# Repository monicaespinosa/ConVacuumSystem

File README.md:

# ConVacuumSystem
Later I will have time to explain what this is about. Let's start with the important things.

## Current circuit
The circuit (still to try) goes as following:

The setup still has to be simulated to find out V_c and to check the accuracy of the voltages selected for the grid and the plate.

## CST Simulations of the setup
The following setup was simulated:

Initially were the following voltages set:
* V_S 6.4 V
* V_C: 6.4 V
* V_G= 400 V
* V_P= 1000 V

The result for the obtained trajectory is shown below. The obtained current was around 5 mA.

However, the shape of the electron beams seems to change its shape in a very drastic way. Making the V_C smaller (more negative) should help concentring more the electrons to the center of the beam. A second simulation was made sweeping the voltage of the Wehnelt_Cylinider between -10 V and 6 V. 

As a result, the following charges on the plate were obtained:

Particles that come out of the coil:

They are only high when the voltage at the Wehnelt Cylinider is equal or higher than that of the coil. A new simulation sweeping Vc between 6.4V and 15.4V is been made. Results:

Evidently, the current (and as a consequence the particles getting to the plate) exists only when V_C>=V_S. The trajectories of the particles change however as they seem to be pushed into the cylinder (because of the higher voltage):

A new simulation setting the voltage on the grid V_G=800 V, putting a porcelain cylinder around the components (to simulate the glass cylinider) and moving the cylinider along the z-axis was made. The obtained trajectories are:

### Setting the voltage on the plate nearly to 0
Simulation with V_G = 1000 V and V_P = 4 V, and moving the cylinder to its initial position.

Simulation with the same parameters but moving the cylinder so its positioned closer to the plate.

Final simulation moving the cylinder back again and setting its voltage to -V_S.

### Variations of the voltage on the plate

Current incoming to the plate is the import_2 current.

Incoming particles:

### Changing the cathode
For all the following simulations the following voltages are set: V_S=6.4V, V_C=-30V V_G = 1000V and V_P = 4V.

#### Vertical filled PEC cylinder
Model:

Trajectories:

Total current leaving the cathode: 1.191e-03 mA

### Vertical hollow PEC cylinder
The cathode looks like the one before but is hollow with a thickness of 0.3 mm.

Trajectories:

Total current leaving the cathode: 9.14e-02 mA

### Toroid
Model:

Trajectories:

Total current leaving the cathode: 0.98 mA

### Rectangular cathode:
Model:

Trajectories: 

Total current leaving the cathode: 0.78 mA

### Sphere
Model:

Trajectories:

Total current leaving the cathode: 1.19 mA

### cut Cone:
Model:

It didn't emit any current when being put this way. However, when rotating like this:

The following trajectories are gotten:

Total current leaving the cathode: 0.71 mA

### Electron-gun Cathode
Model: 

It's a "cone" whose two planar circular faces are connected not by a rotated linear surface but a rotated exponential surface so it's internal radious get's thicker in an exponential way along the w axis as w decreases, simulating a pointy trunked cone. It was initially made small but only few particles were accelerated. Increasing its size and getting it closer to the grid produces the following trajectories:

The total current leaving the cathode was 9.35 mA. However the trajectories are messy and very disperse. After trying to move both the cathode and the grid further from the plate, because of the Wehnelt-Cylinder, the particles collide and then get dispersed again, without reaching the plate:

### Toroid-Coil

Model:

Trajectories: (actually a pretty straight beam)

However, the current incoming to the plate was not as high as expected. In this case, a variation of the voltage on the plate was made and the following curve obtained:

A dependency of the current to the voltage on the grid was also tested. The results below show in fact that the highest this voltage is, the highest the current.

As the shape of the beam seems to be well centered, another try using two toroids was given a shot. The model of the cathode goes as following:

As expected, the trajectories:

However the current across the platte is 50 uA. 

### Clapton Coil
This is the coil used normally for vapers. One of these was modelled in CST and looks like this:

The current incoming into the plate is 21.46uA. However, as the clapton coils that are found in the market have typically a diameter of 3.0mm, which for this project is too small. In order to increase the size of the cathode, a few of them can be placed together. For this purpose, four clapton coils forming a loop was simulated:

Trajectories: Not so straight directed to the center of the beam.

Current incoming to the plate: 0.18 mA

## Current measurement

### Methode
As mentioned before, this is the electrical structure of the setup:

The current measurement in between the plate and the voltage source V_p is more detailed here:

The current flowing through R_mess is theorically expected to be around 5mA according to the simulations. Supposing that the current is 10mA, the following circuit was simulated to choose the value of R_mess:

The voltage across Rm increases as Rm does. A value of Rm=140 ohm is temporarily chosen.

The following component is a amplifier that measures the voltage across the resistor R_mess and whose output is a digital signal whose amount of 1's is proportional to the current flowing through R_mess. The used amplifier is the Si8946A, that measures voltages between -62.5 mV and +62.5 mV, and whose output has a frequency of 10MHz. As this frequency is too high for a microcontroller like Arduino to read, a phase of signal conditioning is required. The simple RC filter produces an analog signal which corresponds to an average value of the quantity of 1's contained in the digital output of the amplifier. As this output is either a 0 or a 1, the analog response of the filter varies between 0V to 1V. However, as we intend to read this signal with Arduino, in order to take of advantage of all its measuring range the to-be-measured signal should be in the full range of 0V to 5V. This is the reason why an additional operational amplifier with a gain of 5 is used. The amplifier corresponds to the TLV9001 by Texas Instruments.

### PCB

The whole circuitry mentioned above, intended to be used for measuring the current caused by the electrons colliding into the plate and further flowing through R_mess, will be designed to be as close as posible to the plate. As not only the amount of current is important, but also the distribution of the electrons along the plate, this last is eventually going to be divided into many smaller plates whose incoming current will be measured separatedly. The first PCB designed to try the measuring circuitry has three plates. The PCB has two layers, one of them containing the plates

and the other one the Si8946A amplifiers and the connector in charge of providing feeding voltage and of letting the signals out. 

To know if the digital signal at 10 MHz is able to be carried by a normal jumper cable without using a SMA connector, some calculations need to be made:

Let's assume a square wave and use Bogatins rule of thumb [here](https://www.edn.com/rule-of-thumb-1-bandwidth-of-a-signal-from-its-rise-time/). According to the datasheet, the rise time is 20ns. The bandwidth of such a signal is 50 MHz, whose wavelength in free space is 6m, let's say 3m in the PCB. At 1/10th wavelength that's 30cm, which sets the upper limit to the jumper wire's length. 

Another option is to attach a second PCB using a PCB to PCB connector. 

>>>>>>> main

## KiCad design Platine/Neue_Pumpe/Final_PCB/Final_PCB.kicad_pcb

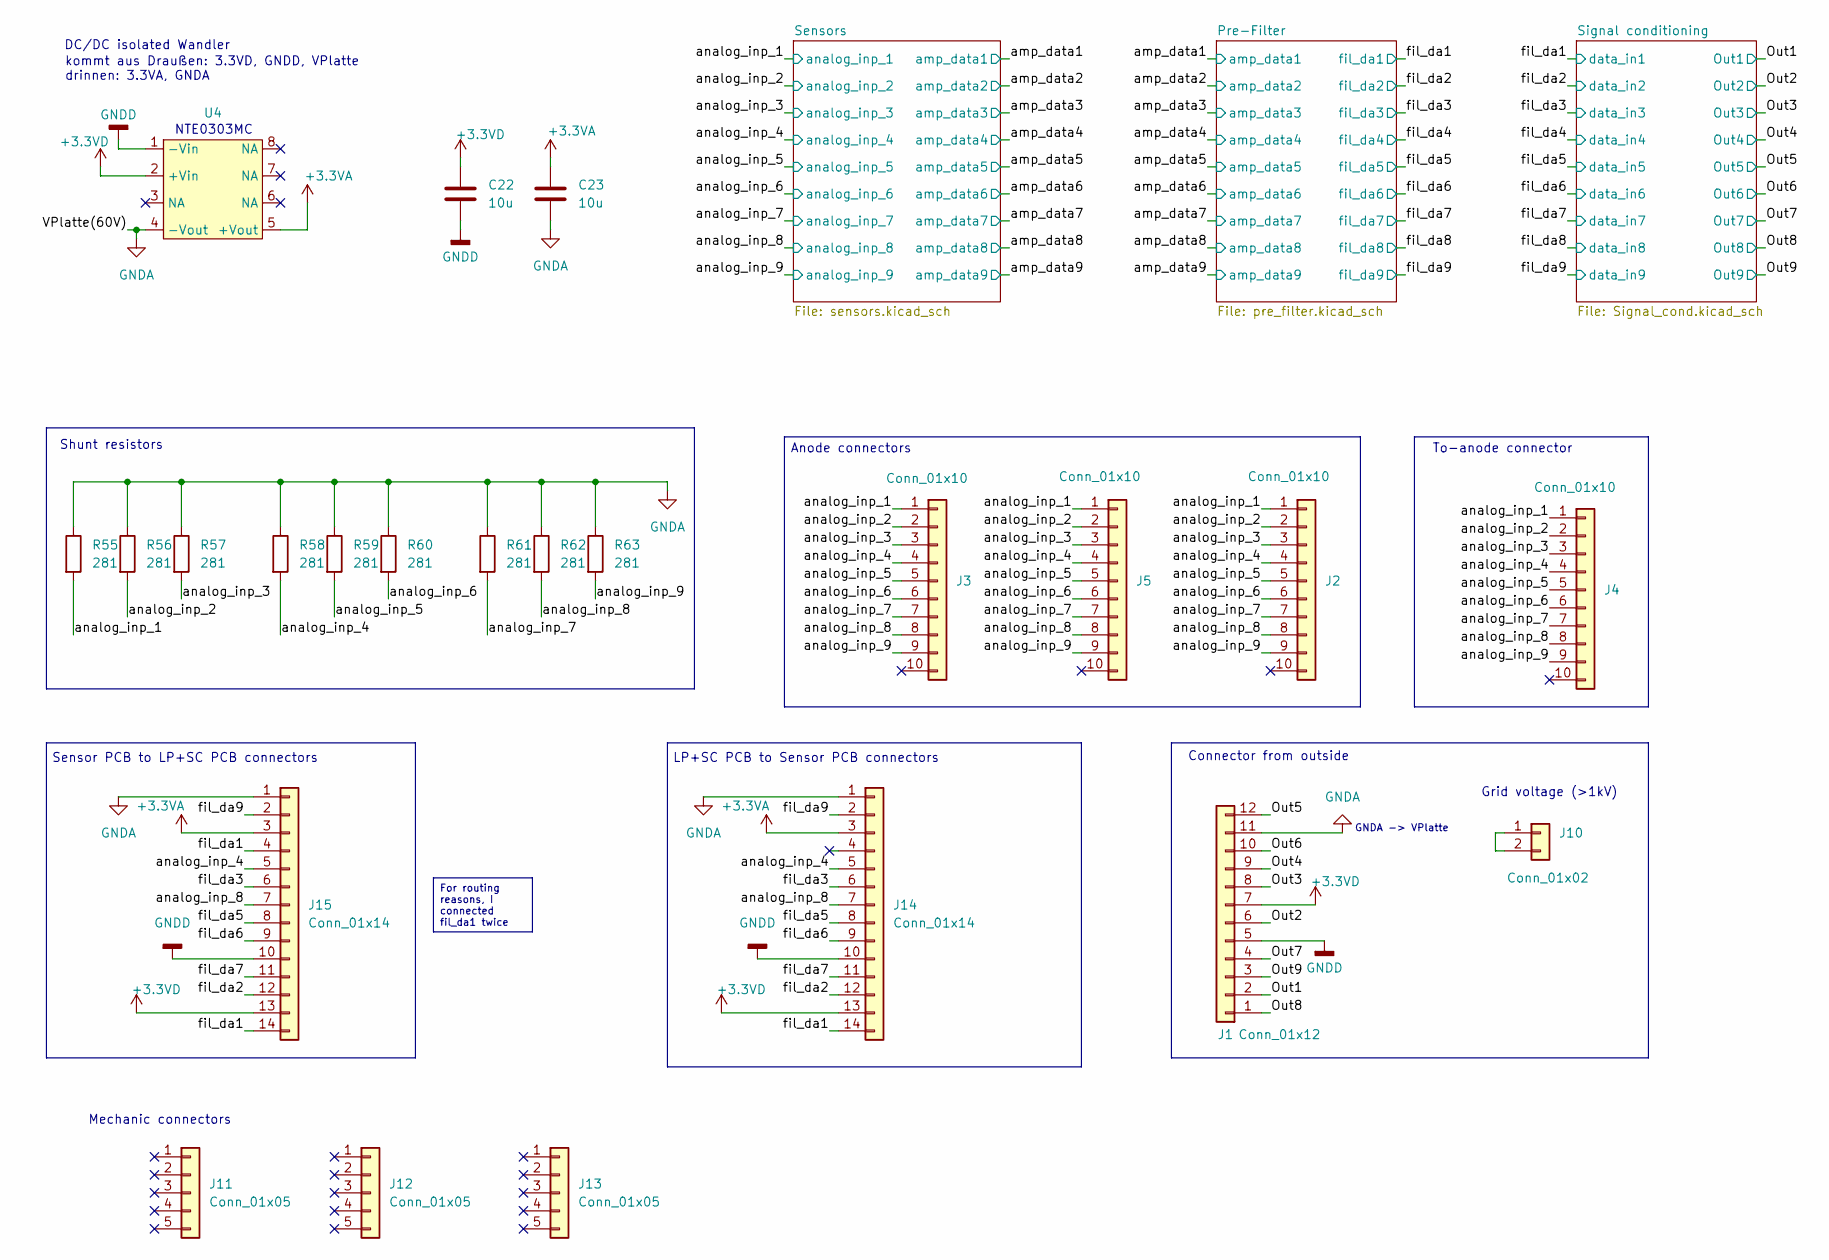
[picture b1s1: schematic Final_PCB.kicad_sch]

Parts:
C22, C23: 10u; C_0603_1608Metric_Pad1.08x0.95mm_HandSolder
J1: Conn_01x12; SHF-106-01-L-D-SM
J2, J3, J5: Conn_01x10; FLE-105-01-X-DV-Y-TR
J4: Conn_01x10; FTSH-105-01-L-DV-K
J10: Conn_01x02; OST_OSTTE020104
J11, J12, J13: Conn_01x05; PinHeader_1x05_P1.27mm_Vertical
J14: Conn_01x14; SAMTEC_FTS-107-01-L-D
J15: Conn_01x14; SAMTEC_FTSH-107-01-L-DV-K
R55, R56, R57, R58, R59, R60, R61, R62, R63: 281; R_0603_1608Metric_Pad0.98x0.95mm_HandSolder
U4: SMDIP-8_W9.53mm

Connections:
+3.3VA: C23.2, J14.3, J15.3, U4.5 (+Vout); also elsewhere on the board
+3.3VD: C22.2, J1.7, J14.13, J15.13, U4.2 (+Vin); also elsewhere on the board
/Out1: J1.2; also elsewhere on the board
/Out2: J1.6; also elsewhere on the board
/Out3: J1.8; also elsewhere on the board
/Out4: J1.9; also elsewhere on the board
/Out5: J1.12; also elsewhere on the board
/Out6: J1.10; also elsewhere on the board
/Out7: J1.4; also elsewhere on the board
/Out8: J1.1; also elsewhere on the board
/Out9: J1.3; also elsewhere on the board
/analog_inp_1: J2.1, J3.1, J4.1, J5.1, R55.2; also elsewhere on the board
/analog_inp_2: J2.2, J3.2, J4.2, J5.2, R56.2; also elsewhere on the board
/analog_inp_3: J2.3, J3.3, J4.3, J5.3, R57.2; also elsewhere on the board
/analog_inp_4: J2.4, J3.4, J4.4, J5.4, J14.5, J15.5, R58.2; also elsewhere on the board
/analog_inp_5: J2.5, J3.5, J4.5, J5.5, R59.2; also elsewhere on the board
/analog_inp_6: J2.6, J3.6, J4.6, J5.6, R60.2; also elsewhere on the board
/analog_inp_7: J2.7, J3.7, J4.7, J5.7, R61.2; also elsewhere on the board
/analog_inp_8: J2.8, J3.8, J4.8, J5.8, J14.7, J15.7, R62.2; also elsewhere on the board
/analog_inp_9: J2.9, J3.9, J4.9, J5.9, R63.2; also elsewhere on the board
/fil_da1: J14.14, J15.4, J15.14; also elsewhere on the board
/fil_da2: J14.12, J15.12; also elsewhere on the board
/fil_da3: J14.6, J15.6; also elsewhere on the board
/fil_da5: J14.8, J15.8; also elsewhere on the board
/fil_da6: J14.9, J15.9; also elsewhere on the board
/fil_da7: J14.11, J15.11; also elsewhere on the board
/fil_da9: J14.2, J15.2; also elsewhere on the board
GNDA: C23.1, J1.11, J14.1, J15.1, R55.1, R56.1, R57.1, R58.1, R59.1, R60.1, R61.1, R62.1, R63.1, U4.4 (-Vout); also elsewhere on the board
GNDD: C22.1, J1.5, J14.10, J15.10, U4.1 (-Vin); also elsewhere on the board
unnamed: J10.1, J10.2

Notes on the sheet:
For routing reasons, I connected fil_da1 twice
Anode connectors
GNDA -> VPlatte
Mechanic connectors
kommt aus Draußen: 3.3VD, GNDD, VPlatte drinnen: 3.3VA, GNDA
Shunt resistors
To-anode connector
Sensor PCB to LP+SC PCB connectors
LP+SC PCB to Sensor PCB connectors
Grid voltage (>1kV)
DC/DC isolated Wandler
Connector from outside
NTE0303MC

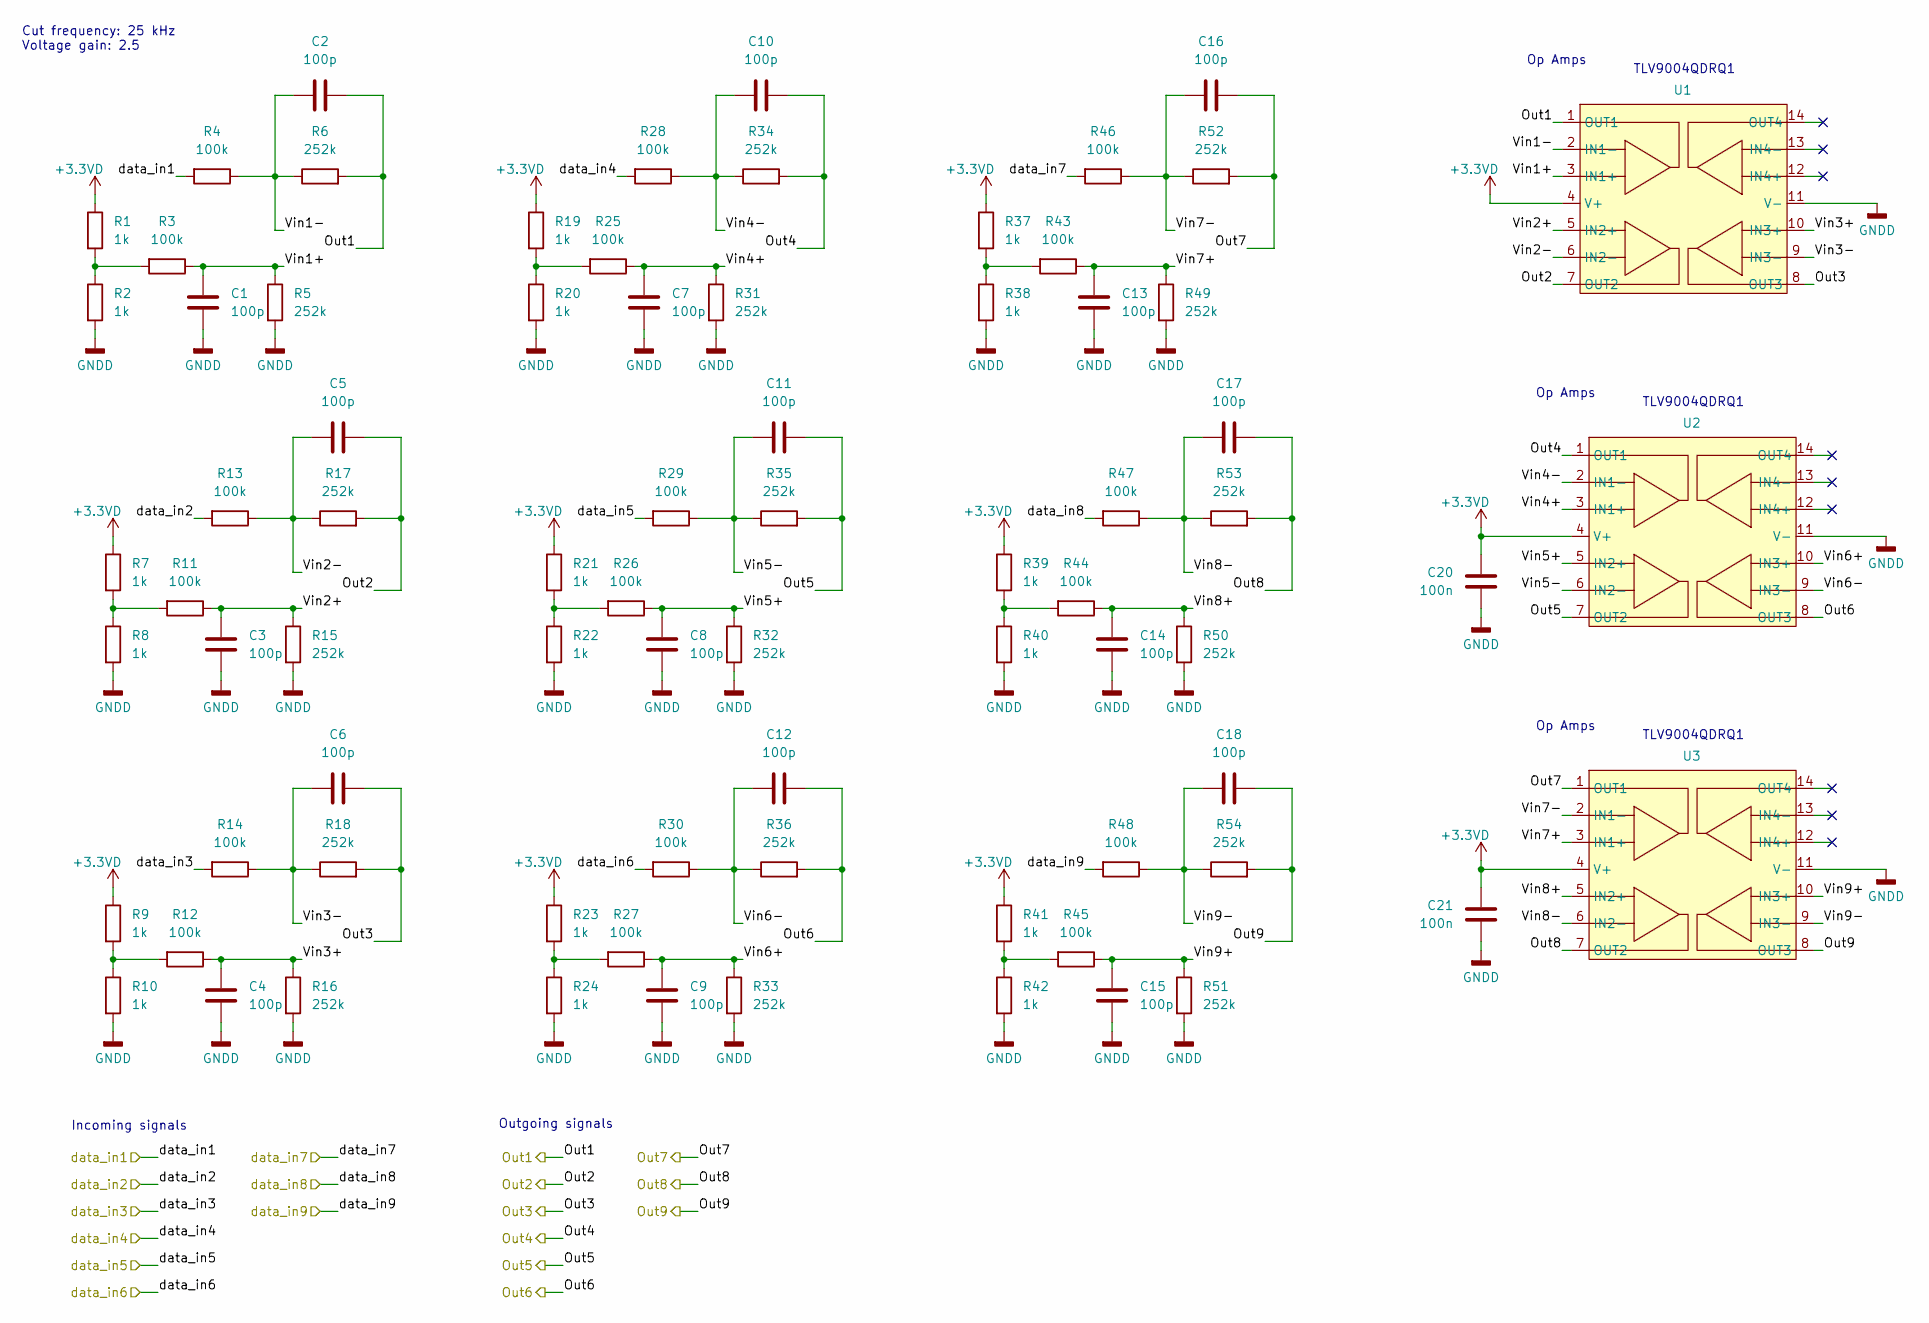
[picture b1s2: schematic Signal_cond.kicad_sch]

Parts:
C1, C2, C3, C4, C5, C6, C7, C8, C9, C10, C11, C12, C13, C14, C15, C16, C17, C18: 100p; C_0603_1608Metric_Pad1.08x0.95mm_HandSolder
C20, C21: 100n; C_0603_1608Metric_Pad1.08x0.95mm_HandSolder
R1, R2, R7, R8, R9, R10, R19, R20, R21, R22, R23, R24, R37, R38, R39, R40, R41, R42: 1k; R_0603_1608Metric_Pad0.98x0.95mm_HandSolder
R3, R4, R11, R12, R13, R14, R25, R26, R27, R28, R29, R30, R43, R44, R45, R46, R47, R48: 100k; R_0603_1608Metric_Pad0.98x0.95mm_HandSolder
R5, R6, R15, R16, R17, R18, R31, R32, R33, R34, R35, R36, R49, R50, R51, R52, R53, R54: 252k; R_0603_1608Metric_Pad0.98x0.95mm_HandSolder
U1, U2, U3: SOIC-14_3.9x8.7mm_P1.27mm

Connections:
+3.3VD: C20.2, C21.2, R1.1, R7.1, R9.1, R19.1, R21.1, R23.1, R37.1, R39.1, R41.1, U1.4 (V+), U2.4 (V+), U3.4 (V+); also elsewhere on the board
/Out1: C2.1, R6.2, U1.1 (OUT1); also elsewhere on the board
/Out2: C5.1, R17.2, U1.7 (OUT2); also elsewhere on the board
/Out3: C6.1, R18.2, U1.8 (OUT3); also elsewhere on the board
/Out4: C10.1, R34.2, U2.1 (OUT1); also elsewhere on the board
/Out5: C11.1, R35.2, U2.7 (OUT2); also elsewhere on the board
/Out6: C12.1, R36.2, U2.8 (OUT3); also elsewhere on the board
/Out7: C16.1, R52.2, U3.1 (OUT1); also elsewhere on the board
/Out8: C17.1, R53.2, U3.7 (OUT2); also elsewhere on the board
/Out9: C18.1, R54.2, U3.8 (OUT3); also elsewhere on the board
/Signal conditioning/Vin1+: C1.2, R3.1, R5.1, U1.3 (IN1+)
/Signal conditioning/Vin1-: C2.2, R4.1, R6.1, U1.2 (IN1-)
/Signal conditioning/Vin2+: C3.2, R11.1, R15.1, U1.5 (IN2+)
/Signal conditioning/Vin2-: C5.2, R13.1, R17.1, U1.6 (IN2-)
/Signal conditioning/Vin3+: C4.2, R12.1, R16.1, U1.10 (IN3+)
/Signal conditioning/Vin3-: C6.2, R14.1, R18.1, U1.9 (IN3-)
/Signal conditioning/Vin4+: C7.2, R25.1, R31.1, U2.3 (IN1+)
/Signal conditioning/Vin4-: C10.2, R28.1, R34.1, U2.2 (IN1-)
/Signal conditioning/Vin5+: C8.2, R26.1, R32.1, U2.5 (IN2+)
/Signal conditioning/Vin5-: C11.2, R29.1, R35.1, U2.6 (IN2-)
/Signal conditioning/Vin6+: C9.2, R27.1, R33.1, U2.10 (IN3+)
/Signal conditioning/Vin6-: C12.2, R30.1, R36.1, U2.9 (IN3-)
/Signal conditioning/Vin7+: C13.2, R43.1, R49.1, U3.3 (IN1+)
/Signal conditioning/Vin7-: C16.2, R46.1, R52.1, U3.2 (IN1-)
/Signal conditioning/Vin8+: C14.2, R44.1, R50.1, U3.5 (IN2+)
/Signal conditioning/Vin8-: C17.2, R47.1, R53.1, U3.6 (IN2-)
/Signal conditioning/Vin9+: C15.2, R45.1, R51.1, U3.10 (IN3+)
/Signal conditioning/Vin9-: C18.2, R48.1, R54.1, U3.9 (IN3-)
/fil_da1: R4.2; also elsewhere on the board
/fil_da2: R13.2; also elsewhere on the board
/fil_da3: R14.2; also elsewhere on the board
/fil_da4: R28.2; also elsewhere on the board
/fil_da5: R29.2; also elsewhere on the board
/fil_da6: R30.2; also elsewhere on the board
/fil_da7: R46.2; also elsewhere on the board
/fil_da8: R47.2; also elsewhere on the board
/fil_da9: R48.2; also elsewhere on the board
GNDD: C1.1, C3.1, C4.1, C7.1, C8.1, C9.1, C13.1, C14.1, C15.1, C20.1, C21.1, R2.2, R5.2, R8.2, R10.2, R15.2, R16.2, R20.2, R22.2, R24.2, R31.2, R32.2, R33.2, R38.2, R40.2, R42.2, R49.2, R50.2, R51.2, U1.11 (V-), U2.11 (V-), U3.11 (V-); also elsewhere on the board
unnamed: R1.2, R2.1, R3.2
unnamed: R9.2, R10.1, R12.2
unnamed: R7.2, R8.1, R11.2
unnamed: R19.2, R20.1, R25.2
unnamed: R21.2, R22.1, R26.2
unnamed: R23.2, R24.1, R27.2
unnamed: R37.2, R38.1, R43.2
unnamed: R39.2, R40.1, R44.2
unnamed: R41.2, R42.1, R45.2

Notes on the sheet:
Op Amps
Cut frequency: 25 kHz Voltage gain: 2.5
TLV9004QDRQ1
Outgoing signals
Incoming signals

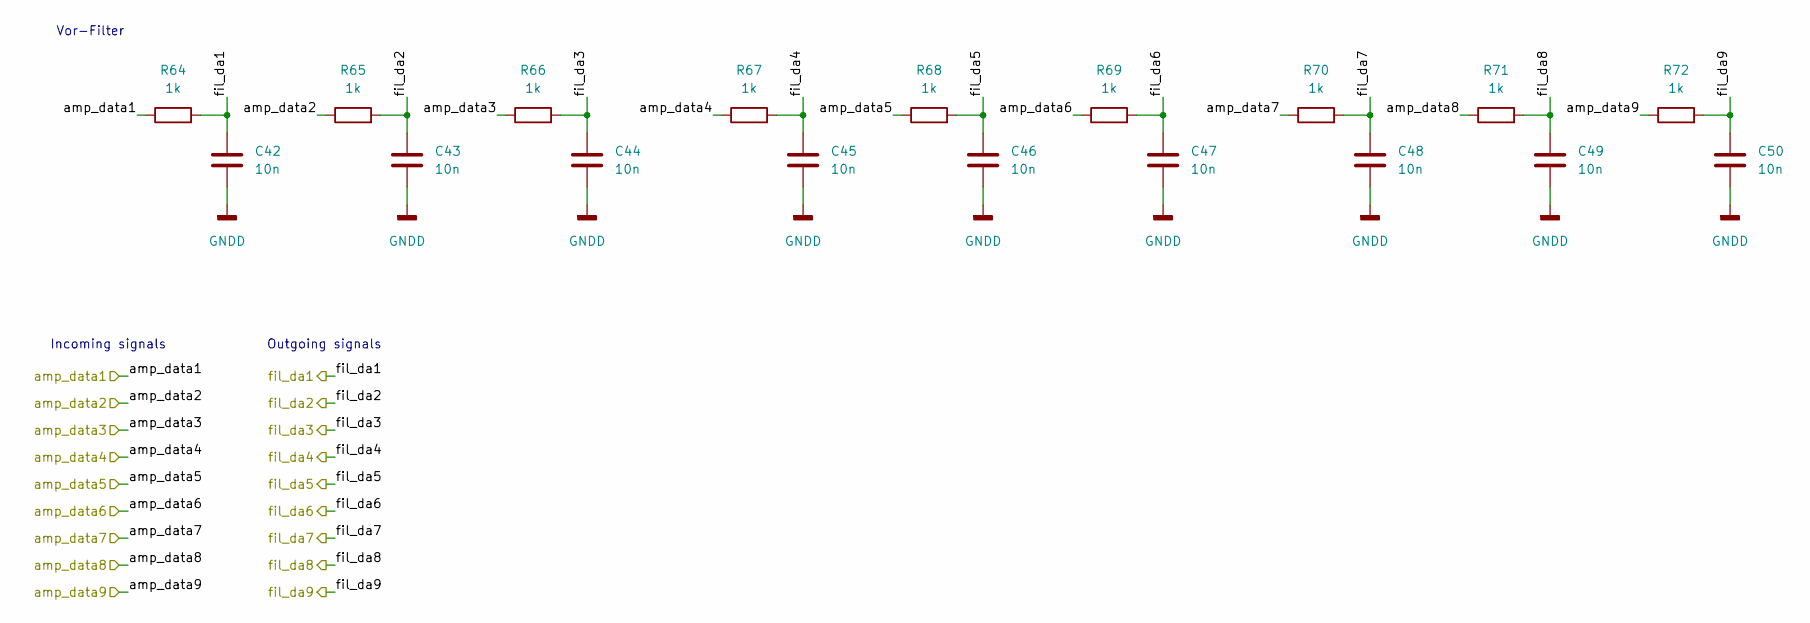
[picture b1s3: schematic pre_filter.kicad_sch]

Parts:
C42, C43, C44, C45, C46, C47, C48, C49, C50: 10n; C_0603_1608Metric_Pad1.08x0.95mm_HandSolder
R64, R65, R66, R67, R68, R69, R70, R71, R72: 1k; R_0603_1608Metric_Pad0.98x0.95mm_HandSolder

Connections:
/amp_data1: R64.1; also elsewhere on the board
/amp_data2: R65.1; also elsewhere on the board
/amp_data3: R66.1; also elsewhere on the board
/amp_data4: R67.1; also elsewhere on the board
/amp_data5: R68.1; also elsewhere on the board
/amp_data6: R69.1; also elsewhere on the board
/amp_data7: R70.1; also elsewhere on the board
/amp_data8: R71.1; also elsewhere on the board
/amp_data9: R72.1; also elsewhere on the board
/fil_da1: C42.1, R64.2; also elsewhere on the board
/fil_da2: C43.1, R65.2; also elsewhere on the board
/fil_da3: C44.1, R66.2; also elsewhere on the board
/fil_da4: C45.1, R67.2; also elsewhere on the board
/fil_da5: C46.1, R68.2; also elsewhere on the board
/fil_da6: C47.1, R69.2; also elsewhere on the board
/fil_da7: C48.1, R70.2; also elsewhere on the board
/fil_da8: C49.1, R71.2; also elsewhere on the board
/fil_da9: C50.1, R72.2; also elsewhere on the board
GNDD: C42.2, C43.2, C44.2, C45.2, C46.2, C47.2, C48.2, C49.2, C50.2; also elsewhere on the board

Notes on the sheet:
Vor-Filter
Outgoing signals
Incoming signals

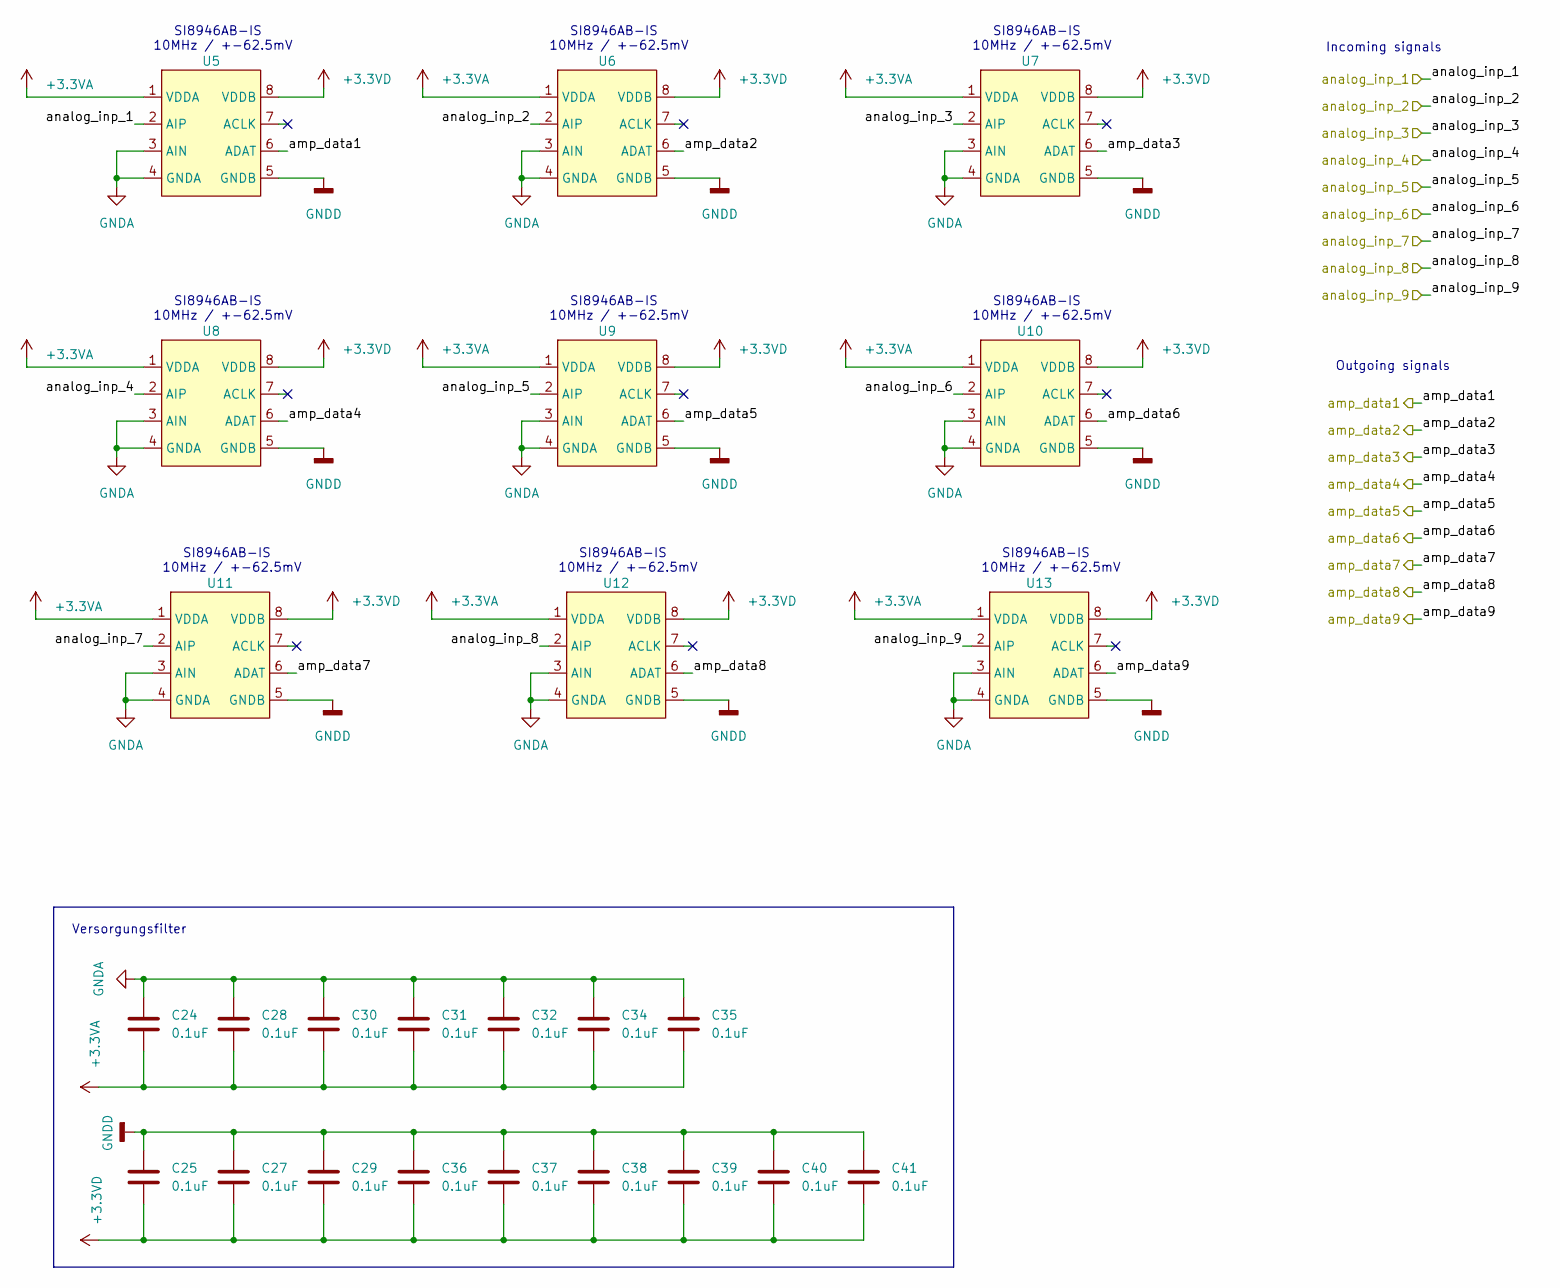
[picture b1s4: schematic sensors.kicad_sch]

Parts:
C24, C25, C27, C28, C29, C30, C31, C32, C34, C35, C36, C37, C38, C39, C40, C41: 0.1uF; C_0603_1608Metric_Pad1.08x0.95mm_HandSolder
U5, U6, U7, U8, U9, U10, U11, U12, U13: SOP-8_3.9x4.9mm_P1.27mm

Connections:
+3.3VA: C24.2, C28.2, C30.2, C31.2, C32.2, C34.2, C35.2, U5.1 (VDDA), U6.1 (VDDA), U7.1 (VDDA), U8.1 (VDDA), U9.1 (VDDA), U10.1 (VDDA), U11.1 (VDDA), U12.1 (VDDA), U13.1 (VDDA); also elsewhere on the board
+3.3VD: C25.2, C27.2, C29.2, C36.2, C37.2, C38.2, C39.2, C40.2, C41.2, U5.8 (VDDB), U6.8 (VDDB), U7.8 (VDDB), U8.8 (VDDB), U9.8 (VDDB), U10.8 (VDDB), U11.8 (VDDB), U12.8 (VDDB), U13.8 (VDDB); also elsewhere on the board
/amp_data1: U5.6 (ADAT); also elsewhere on the board
/amp_data2: U6.6 (ADAT); also elsewhere on the board
/amp_data3: U7.6 (ADAT); also elsewhere on the board
/amp_data4: U8.6 (ADAT); also elsewhere on the board
/amp_data5: U9.6 (ADAT); also elsewhere on the board
/amp_data6: U10.6 (ADAT); also elsewhere on the board
/amp_data7: U11.6 (ADAT); also elsewhere on the board
/amp_data8: U12.6 (ADAT); also elsewhere on the board
/amp_data9: U13.6 (ADAT); also elsewhere on the board
/analog_inp_1: U5.2 (AIP); also elsewhere on the board
/analog_inp_2: U6.2 (AIP); also elsewhere on the board
/analog_inp_3: U7.2 (AIP); also elsewhere on the board
/analog_inp_4: U8.2 (AIP); also elsewhere on the board
/analog_inp_5: U9.2 (AIP); also elsewhere on the board
/analog_inp_6: U10.2 (AIP); also elsewhere on the board
/analog_inp_7: U11.2 (AIP); also elsewhere on the board
/analog_inp_8: U12.2 (AIP); also elsewhere on the board
/analog_inp_9: U13.2 (AIP); also elsewhere on the board
GNDA: C24.1, C28.1, C30.1, C31.1, C32.1, C34.1, C35.1, U5.3 (AIN), U5.4 (GNDA), U6.3 (AIN), U6.4 (GNDA), U7.3 (AIN), U7.4 (GNDA), U8.3 (AIN), U8.4 (GNDA), U9.3 (AIN), U9.4 (GNDA), U10.3 (AIN), U10.4 (GNDA), U11.3 (AIN), U11.4 (GNDA), U12.3 (AIN), U12.4 (GNDA), U13.3 (AIN), U13.4 (GNDA); also elsewhere on the board
GNDD: C25.1, C27.1, C29.1, C36.1, C37.1, C38.1, C39.1, C40.1, C41.1, U5.5 (GNDB), U6.5 (GNDB), U7.5 (GNDB), U8.5 (GNDB), U9.5 (GNDB), U10.5 (GNDB), U11.5 (GNDB), U12.5 (GNDB), U13.5 (GNDB); also elsewhere on the board

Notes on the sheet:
Incoming signals
SI8946AB-IS 10MHz / +-62.5mV
Versorgungsfilter
Outgoing signals

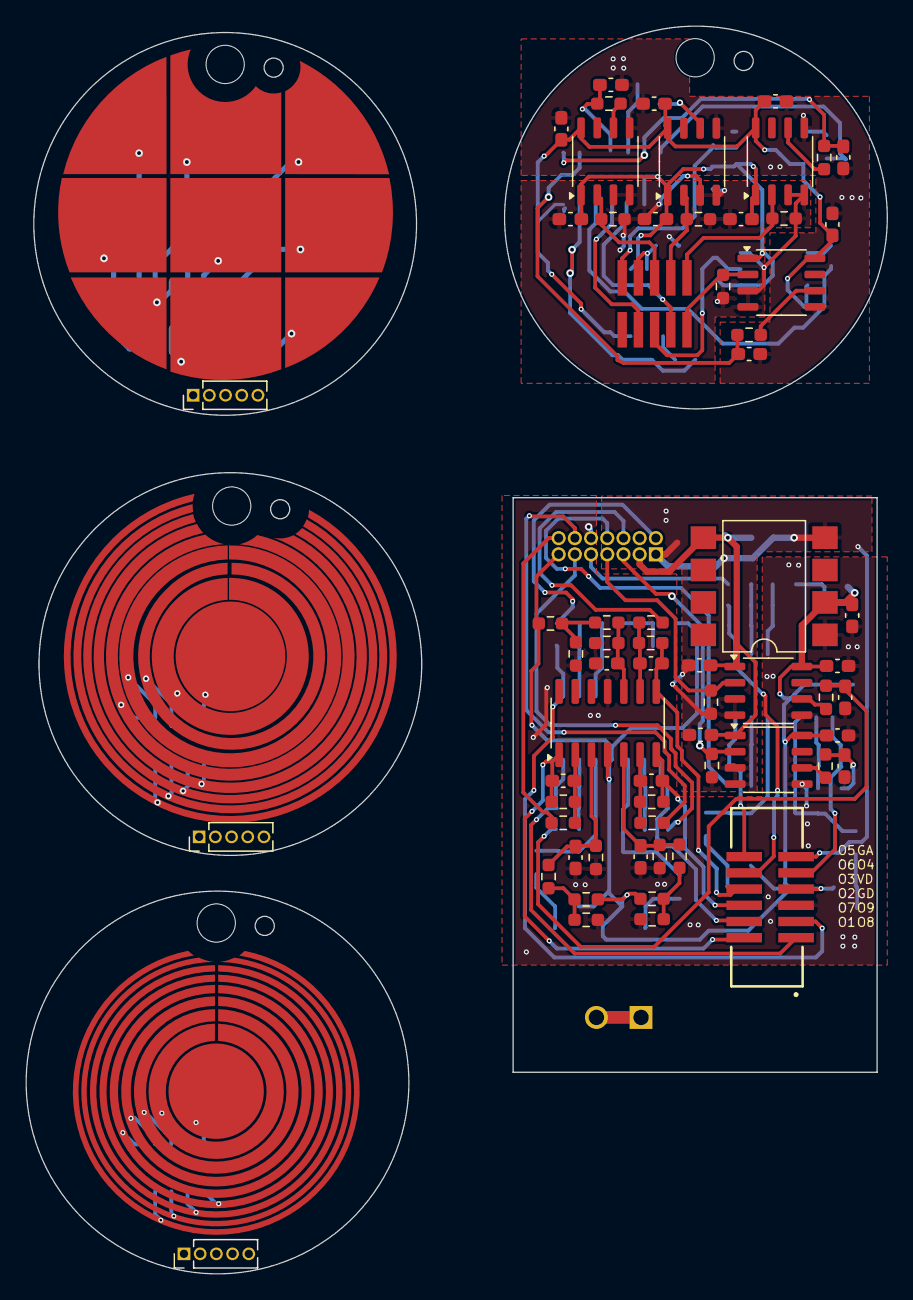
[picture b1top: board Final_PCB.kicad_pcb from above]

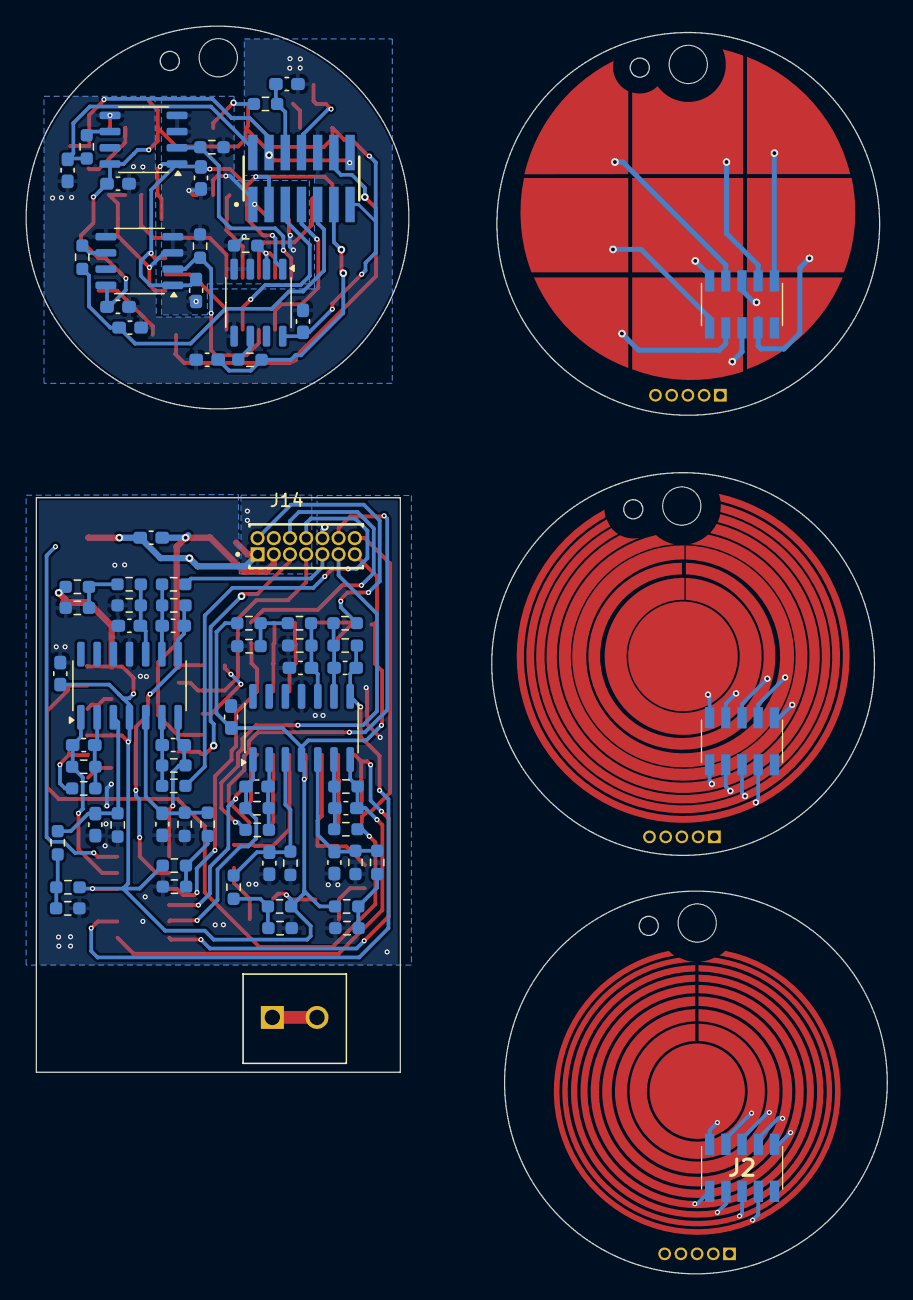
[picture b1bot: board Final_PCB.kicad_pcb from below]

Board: 2 copper layers, 67.5 x 97.8 mm, 143 parts (78 on the bottom side), 68 nets.

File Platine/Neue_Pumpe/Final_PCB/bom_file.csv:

"Reference","Value","Datasheet","Footprint","Qty","DNP"
"C1,C2,C3,C4,C5,C6,C7,C8,C9,C10,C11,C12,C13,C14,C15,C16,C17,C18","100p","~","Capacitor_SMD:C_0603_1608Metric_Pad1.08x0.95mm_HandSolder","18",""
"C20,C21","100n","~","Capacitor_SMD:C_0603_1608Metric_Pad1.08x0.95mm_HandSolder","2",""
"C22,C23","10u","~","Capacitor_SMD:C_0603_1608Metric_Pad1.08x0.95mm_HandSolder","2",""
"C24,C25,C27,C28,C29,C30,C31,C32,C34,C35,C36,C37,C38,C39,C40,C41","0.1uF","~","Capacitor_SMD:C_0603_1608Metric_Pad1.08x0.95mm_HandSolder","16",""
"C42,C43,C44,C45,C46,C47,C48,C49,C50","10n","~","Capacitor_SMD:C_0603_1608Metric_Pad1.08x0.95mm_HandSolder","9",""
"J1","Conn_01x12","~","SHF-106-01-L-D-SM:SHF-106-01-L-D-SM","1",""
"J2,J3,J4,J5","Conn_01x10","~","-- verschiedene Werte --","4",""
"J6,J8","Conn_01x08","~","-- verschiedene Werte --","2",""
"J7,J9","Conn_01x06","~","-- verschiedene Werte --","2",""
"J10","Conn_01x02","~","OSTTE020104:OST_OSTTE020104","1",""
"R1,R2,R7,R8,R9,R10,R19,R20,R21,R22,R23,R24,R37,R38,R39,R40,R41,R42,R64,R65,R66,R67,R68,R69,R70,R71,R72","1k","~","Resistor_SMD:R_0603_1608Metric_Pad0.98x0.95mm_HandSolder","27",""
"R3,R4,R11,R12,R13,R14,R25,R26,R27,R28,R29,R30,R43,R44,R45,R46,R47,R48","100k","~","Resistor_SMD:R_0603_1608Metric_Pad0.98x0.95mm_HandSolder","18",""
"R5,R6,R15,R16,R17,R18,R31,R32,R33,R34,R35,R36,R49,R50,R51,R52,R53,R54","252k","~","Resistor_SMD:R_0603_1608Metric_Pad0.98x0.95mm_HandSolder","18",""
"R55,R56,R57,R58,R59,R60,R61,R62,R63","12.5","~","Resistor_SMD:R_0603_1608Metric_Pad0.98x0.95mm_HandSolder","9",""
"U1,U2,U3,U4,U5,U6,U7,U8,U9,U10,U11,U12,U13","~","","-- verschiedene Werte --","13",""

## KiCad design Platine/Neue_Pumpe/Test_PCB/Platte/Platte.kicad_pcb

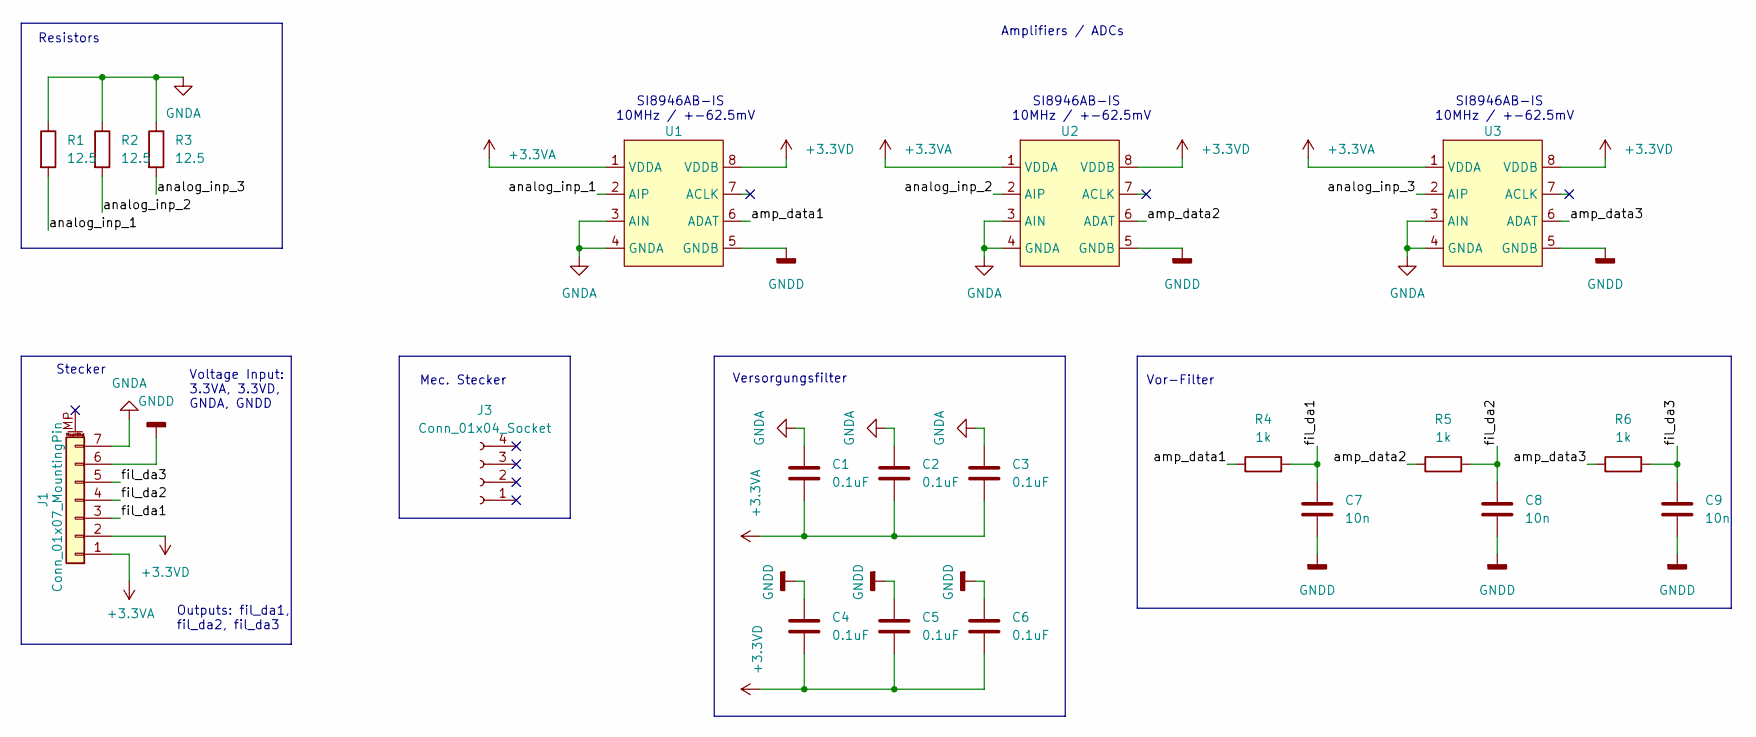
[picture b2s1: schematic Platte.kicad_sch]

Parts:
C1, C2, C3, C4, C5, C6: 0.1uF; C_0603_1608Metric_Pad1.08x0.95mm_HandSolder
C7, C8, C9: 10n; C_0603_1608Metric_Pad1.08x0.95mm_HandSolder
J1: Conn_01x07_MountingPin; JST_GH_BM07B-GHS-TBT_1x07-1MP_P1.25mm_Vertical
J3: Conn_01x04_Socket; PinHeader_1x04_P1.27mm_Vertical
R1, R2, R3: 12.5; R_0603_1608Metric_Pad0.98x0.95mm_HandSolder
R4, R5, R6: 1k; R_0603_1608Metric_Pad0.98x0.95mm_HandSolder
U1, U2, U3: SOP-8_3.9x4.9mm_P1.27mm

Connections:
+3.3VA: C1.2, C2.2, C3.2, J1.1, U1.1 (VDDA), U2.1 (VDDA), U3.1 (VDDA)
+3.3VD: C4.2, C5.2, C6.2, J1.2, U1.8 (VDDB), U2.8 (VDDB), U3.8 (VDDB)
/amp_data1: R4.1, U1.6 (ADAT)
/amp_data2: R5.1, U2.6 (ADAT)
/amp_data3: R6.1, U3.6 (ADAT)
/analog_inp_1: R1.2, U1.2 (AIP)
/analog_inp_2: R2.2, U2.2 (AIP)
/analog_inp_3: R3.2, U3.2 (AIP)
/fil_da1: C7.1, J1.3, R4.2
/fil_da2: C8.1, J1.4, R5.2
/fil_da3: C9.1, J1.5, R6.2
GNDA: C1.1, C2.1, C3.1, J1.7, R1.1, R2.1, R3.1, U1.3 (AIN), U1.4 (GNDA), U2.3 (AIN), U2.4 (GNDA), U3.3 (AIN), U3.4 (GNDA)
GNDD: C4.1, C5.1, C6.1, C7.2, C8.2, C9.2, J1.6, U1.5 (GNDB), U2.5 (GNDB), U3.5 (GNDB)

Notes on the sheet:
SI8946AB-IS 10MHz / +-62.5mV
Resistors
Mec. Stecker
Stecker
Versorgungsfilter
Outputs: fil_da1, fil_da2, fil_da3
Amplifiers / ADCs
Voltage Input: 3.3VA, 3.3VD, GNDA, GNDD
Vor-Filter

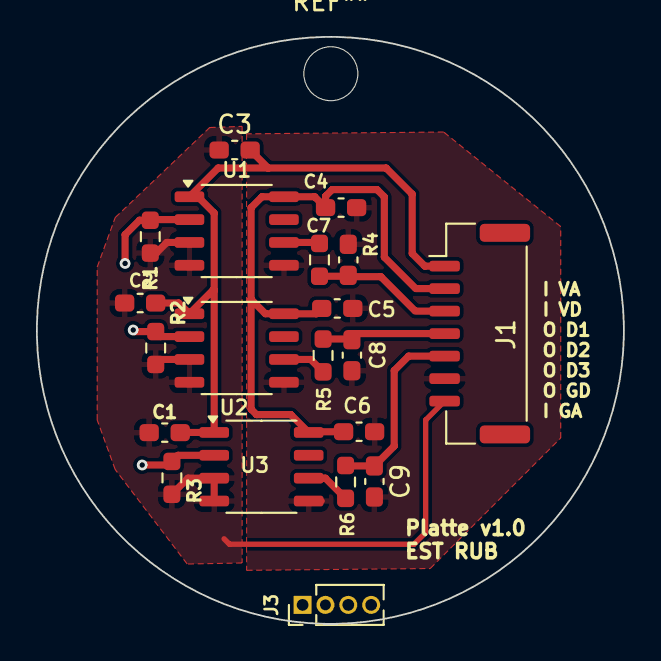
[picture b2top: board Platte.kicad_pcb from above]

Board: 2 copper layers, 32.6 x 32.6 mm, 20 parts (0 on the bottom side), 13 nets.
